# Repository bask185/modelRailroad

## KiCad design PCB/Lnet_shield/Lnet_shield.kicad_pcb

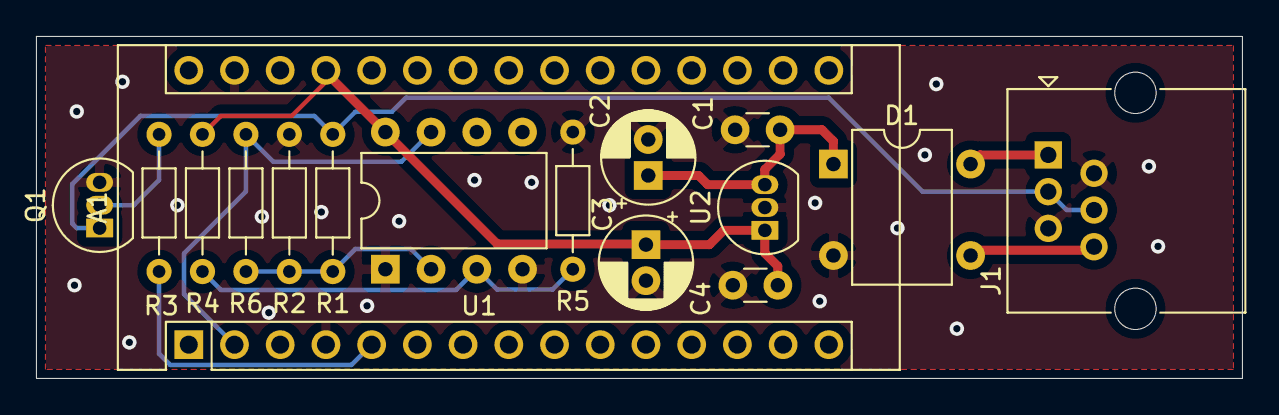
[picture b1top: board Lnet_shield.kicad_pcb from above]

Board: 2 copper layers, 67.0 x 19.0 mm, 16 parts (0 on the bottom side), 11 nets.

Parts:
A1: Arduino_Nano_v2.x; Arduino_Nano
C1, C4: C; C_Disc_D3.0mm_W1.6mm_P2.50mm
C2, C3: CP; CP_Radial_D5.0mm_P2.00mm
D1: D_Bridge_+-AA; Diode_Bridge_DIP-4_W7.62mm_P5.08mm
J1: RJ12; RJ25_Wayconn_MJEA-660X1_Horizontal
Q1: BC547; TO-92_Inline
R1: 47k; R_Axial_DIN0204_L3.6mm_D1.6mm_P7.62mm_Horizontal
R2: 150k; R_Axial_DIN0204_L3.6mm_D1.6mm_P7.62mm_Horizontal
R3: 4k7; R_Axial_DIN0204_L3.6mm_D1.6mm_P7.62mm_Horizontal
R4: 10k; R_Axial_DIN0204_L3.6mm_D1.6mm_P7.62mm_Horizontal
R5: 22k; R_Axial_DIN0204_L3.6mm_D1.6mm_P7.62mm_Horizontal
R6: 220k; R_Axial_DIN0204_L3.6mm_D1.6mm_P7.62mm_Horizontal
U1: LM311; DIP-8_W7.62mm
U2: L78L05_TO92; TO-92_Inline

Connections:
+5V: A1.27, C3.1, C4.1, R4.2, U1.8, U2.1
+12V: C1.1, C2.1, D1.1, U2.3
/Lnet: J1.3, J1.4, Q1.1, R1.2
/Rx: A1.2, R6.1, U1.7
/Tx: A1.5, R3.1
GND: A1.4, A1.29, C1.2, C2.2, C3.2, C4.2, D1.2, J1.2, J1.5, Q1.3, R2.1, R5.1, U1.1, U1.4, U2.2
unnamed: D1.3, J1.6
unnamed: D1.4, J1.1
unnamed: Q1.2, R3.2
unnamed: R1.1, R2.2, R6.2, U1.2
unnamed: R4.1, R5.2, U1.3

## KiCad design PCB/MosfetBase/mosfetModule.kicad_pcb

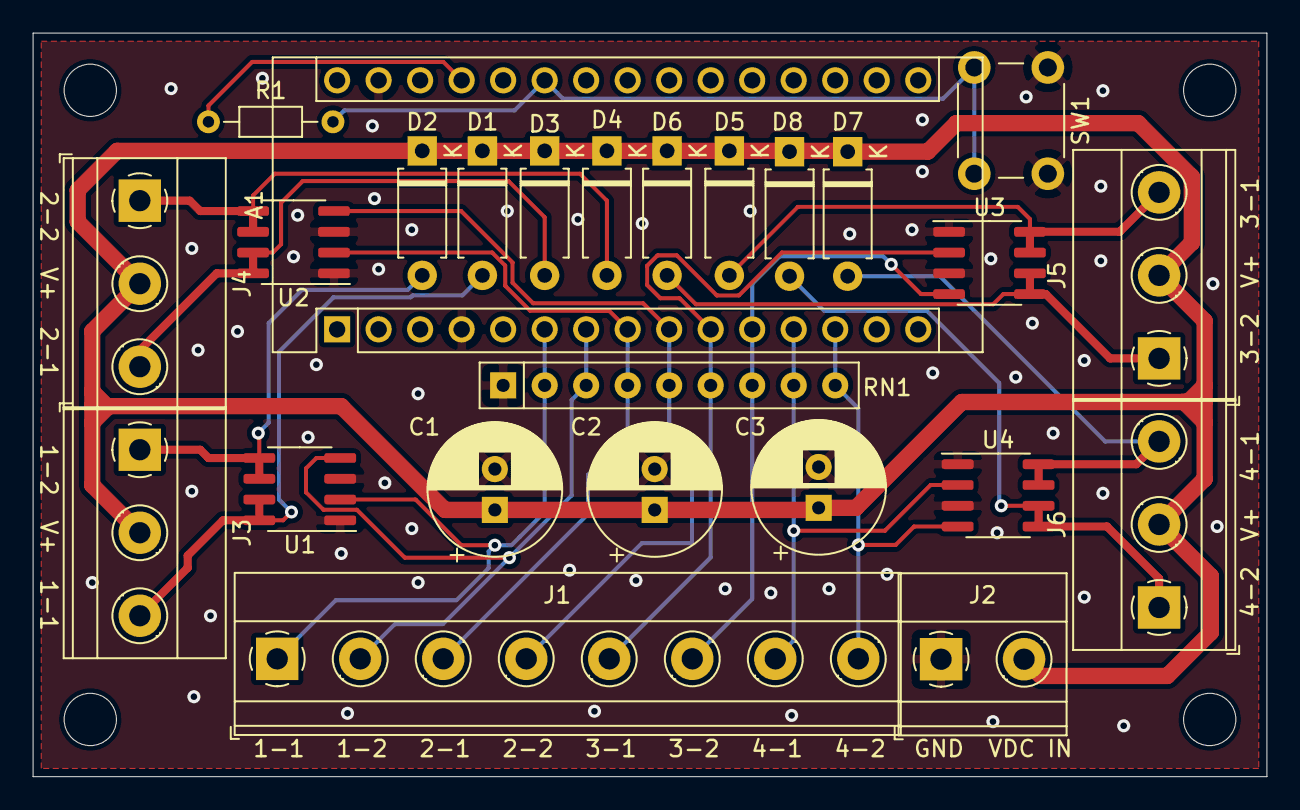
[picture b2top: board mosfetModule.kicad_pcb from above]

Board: 2 copper layers, 75.5 x 45.5 mm, 25 parts (0 on the bottom side), 20 nets.

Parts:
A1: Arduino_Nano_v3.x; Arduino_Nano
C1, C2, C3: CP; CP_Radial_D8.0mm_P2.50mm
D1, D2, D3, D4, D5, D6, D7, D8: D; D_A-405_P7.62mm_Horizontal
J1: toDCCnext; TerminalBlock_Phoenix_MKDS-1,5-8-5.08_1x08_P5.08mm_Horizont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
J2: power; TerminalBlock_Phoenix_MKDS-1,5-2-5.08_1x02_P5.08mm_Horizont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
J3, J4, J5, J6: point; TerminalBlock_Phoenix_MKDS-1,5-3-5.08_1x03_P5.08mm_Horizont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
R1: R; R_Axial_DIN0204_L3.6mm_D1.6mm_P7.62mm_Horizontal
RN1: R; R_Array_SIP9
SW1: SW_SPST; SW_PUSH_6mm_H4.3mm
U1, U2, U3, U4: IRF71xx; SOIC-8_3.9x4.9mm_P1.27mm

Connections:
+5V: A1.27, R1.1
/coil1-1: D1.2, J3.3, U1.7, U1.8
/coil1-2: D2.2, J3.1, U1.5, U1.6
/coil2-1: D3.2, J4.3, U2.7, U2.8
/coil2-2: D4.2, J4.1, U2.5, U2.6
/coil3-1: D5.2, J5.3, U3.7, U3.8
/coil3-2: D6.2, J5.1, U3.5, U3.6
/coil4-1: D7.2, J6.3, U4.7, U4.8
/coil4-2: D8.2, J6.1, U4.5, U4.6
/in1-1: A1.6, J1.1, RN1.2, U1.2
/in1-2: A1.7, J1.2, RN1.3, U1.4
/in2-1: A1.8, J1.3, RN1.4, U2.2
/in2-2: A1.9, J1.4, RN1.5, U2.4
/in3-1: A1.10, J1.5, RN1.6, U3.2
/in3-2: A1.11, J1.6, RN1.7, U3.4
/in4-1: A1.12, J1.7, RN1.8, U4.2
/in4-2: A1.13, J1.8, RN1.9, U4.4
GND: A1.4, A1.29, C1.2, C2.2, C3.2, J2.1, RN1.1, SW1.1, U1.1, U1.3, U2.1, U2.3, U3.1, U3.3, U4.1, U4.3
unnamed: A1.25, R1.2, SW1.2
VCC: C1.1, C2.1, C3.1, D1.1, D2.1, D3.1, D4.1, D5.1, D6.1, D7.1, D8.1, J2.2, J3.2, J4.2, J5.2, J6.2

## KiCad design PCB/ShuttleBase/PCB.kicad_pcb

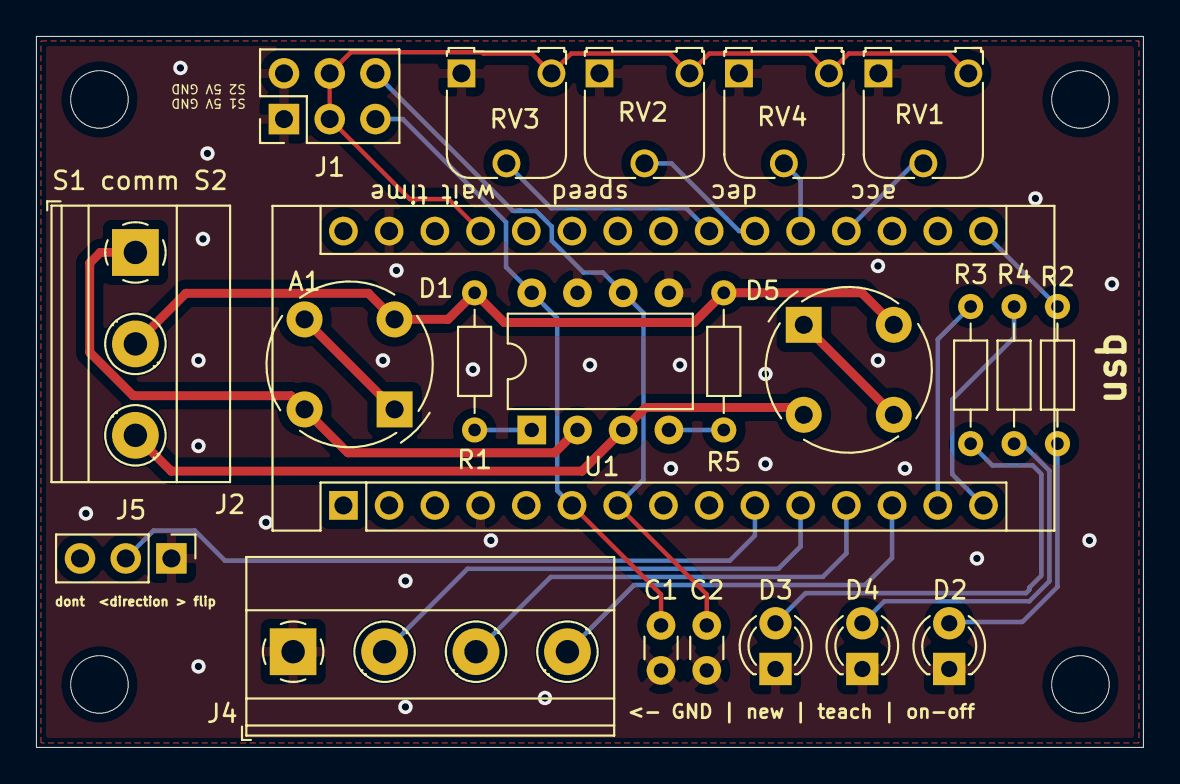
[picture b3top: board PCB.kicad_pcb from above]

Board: 2 copper layers, 61.5 x 39.5 mm, 22 parts (0 on the bottom side), 25 nets.

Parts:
A1: Arduino_Nano_v2.x; Arduino_Nano
C1, C2: C; C_Disc_D3.0mm_W1.6mm_P2.50mm
D1, D5: D; Diode_Bridge_Round_D9.0mm
D2: RED; LED_D3.0mm
D3: GREEN; LED_D3.0mm
D4: YEL; LED_D3.0mm
J1: IR; PinHeader_2x03_P2.54mm_Vertical
J2: detectors; TerminalBlock_Phoenix_MKDS-1,5-3-5.08_1x03_P5.08mm_Horizont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
J4: switches; TerminalBlock_Phoenix_MKDS-1,5-4-5.08_1x04_P5.08mm_Horizont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
J5: directionFlip; PinHeader_1x03_P2.54mm_Vertical
R1, R2, R3, R4, R5: R; R_Axial_DIN0204_L3.6mm_D1.6mm_P7.62mm_Horizontal
RV1, RV2, RV3, RV4: R_POT; Potentiometer_Runtron_RM-065_Vertical
U1: PC827; DIP-8_W7.62mm

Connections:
+5V: A1.27, J1.3, J1.4, RV1.3, RV2.3, RV3.3, RV4.3
/ON_OFF: A1.13, J4.4
/accel: A1.20, RV4.2
/brake: A1.19, RV1.2
/direction: A1.10, J5.2
/greenStatus: A1.14, R3.1
/newTrain: A1.11, J4.2
/redStatus: A1.16, R2.1
/sensor1: A1.6, C1.1, J1.5, U1.8
/sensor2: A1.7, C2.1, J1.6, U1.6
/speed: A1.21, RV2.2
/teach: A1.12, J4.3
/wait: A1.22, RV3.2
/yellowStatus: A1.15, R4.1
GND: A1.4, A1.29, C1.2, C2.2, D2.1, D3.1, D4.1, J1.1, J1.2, J4.1, J5.1, RV1.1, RV2.1, RV3.1, RV4.1, U1.5, U1.7
unnamed: D1.1, D1.3
unnamed: D1.2, D5.4, J2.2, R1.1, R5.2
unnamed: D1.4, J2.1, U1.2
unnamed: D2.2, R2.2
unnamed: D3.2, R3.2
unnamed: D4.2, R4.2
unnamed: D5.1, D5.3
unnamed: D5.2, J2.3, U1.3
unnamed: R1.2, U1.1
unnamed: R5.1, U1.4

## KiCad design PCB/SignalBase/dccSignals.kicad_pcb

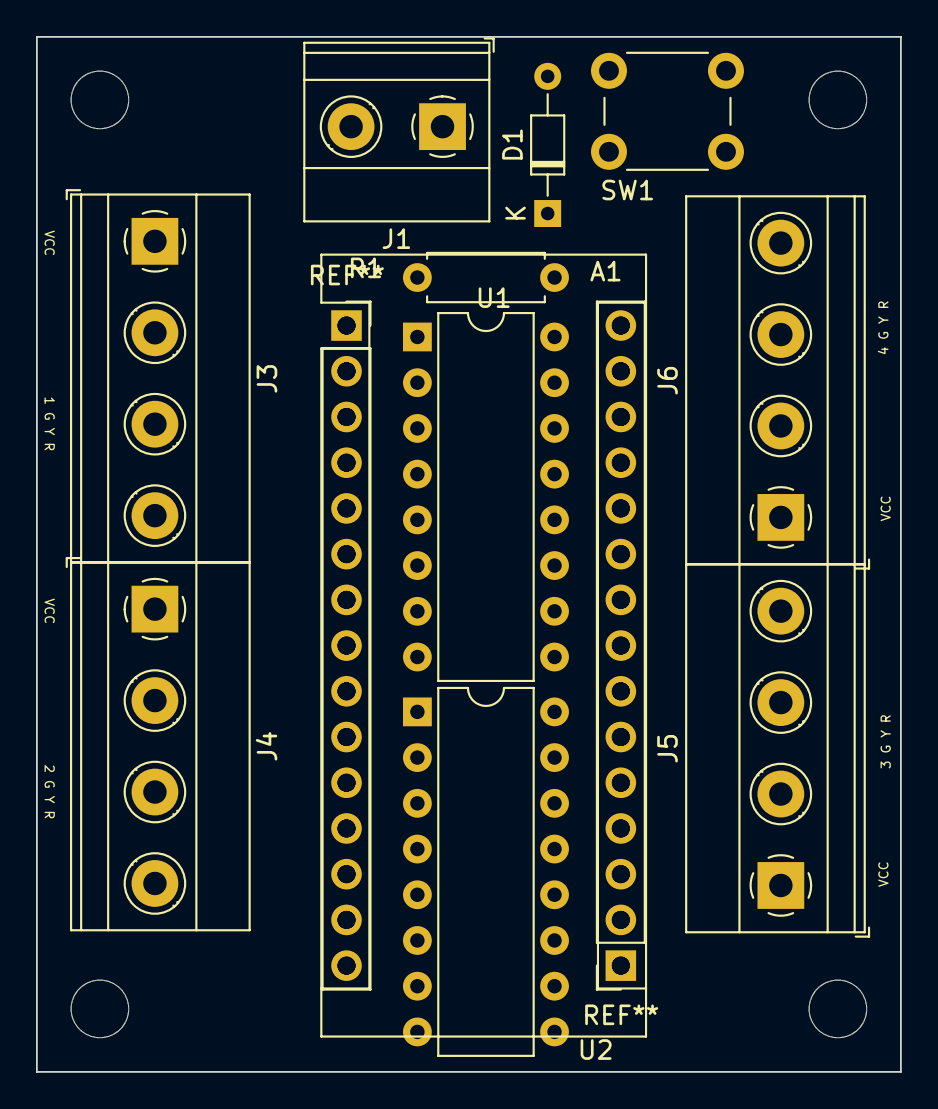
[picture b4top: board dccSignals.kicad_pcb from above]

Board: 2 copper layers, 48.0 x 57.5 mm, 11 parts (0 on the bottom side), 29 nets, no tracks yet.

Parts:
A1: Arduino_Nano_v2.x; Arduino_Nano
D1: D; D_DO-34_SOD68_P7.62mm_Horizontal
J1: Screw_Terminal_01x02; TerminalBlock_Phoenix_MKDS-1,5-2-5.08_1x02_P5.08mm_Horizont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
J3, J4, J5, J6: leds; TerminalBlock_Phoenix_MKDS-1,5-4-5.08_1x04_P5.08mm_Horizont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
R1: R; R_Axial_DIN0207_L6.3mm_D2.5mm_P7.62mm_Horizontal
SW1: SW_SPST; SW_PUSH_6mm_H4.3mm
U1, U2: ULN2003A; DIP-16_W7.62mm

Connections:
+5V: A1.27, R1.1
/S1G: J3.2, U1.16
/S1G_IN: A1.6, U1.1
/S1R: J3.4, U1.14
/S1R_IN: A1.8, U1.3
/S1Y: J3.3, U1.15
/S1Y_IN: A1.7, U1.2
/S2G: J4.2, U1.13
/S2G_IN: A1.9, U1.4
/S2R: J4.4, U1.11
/S2R_IN: A1.11, U1.6
/S2Y: J4.3, U1.12
/S2Y_IN: A1.10, U1.5
/S3G: J5.2, U2.11
/S3G_IN: A1.16, U2.6
/S3R: J5.4, U2.13
/S3R_IN: A1.15, U2.4
/S3Y: J5.3, U2.12
/S3Y_IN: A1.24, U2.5
/S4G: J6.2, U2.14
/S4G_IN: A1.12, U2.1
/S4R: J6.4, U2.16
/S4R_IN: A1.14, U2.3
/S4Y: J6.3, U2.15
/S4Y_IN: A1.13, U2.2
GND: A1.4, A1.29, J1.2, SW1.2, U1.8, U2.8
unnamed: A1.25, R1.2, SW1.1
unnamed: D1.2, J1.1
VCC: D1.1, J3.1, J4.1, J5.1, J6.1, U1.9, U2.9

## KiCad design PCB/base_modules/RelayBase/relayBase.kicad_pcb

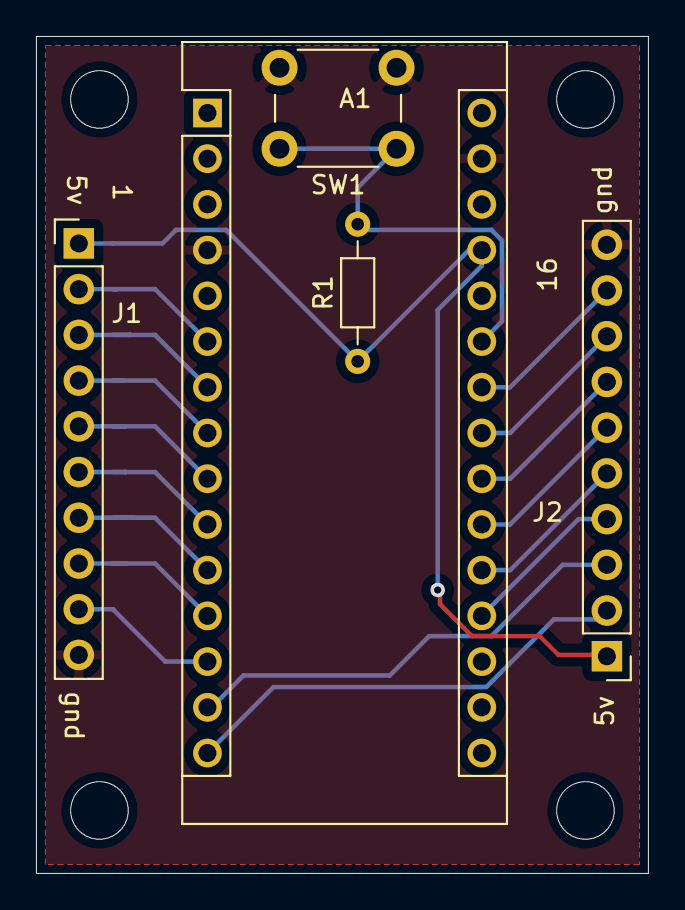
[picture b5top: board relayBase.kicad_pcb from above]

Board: 2 copper layers, 34.0 x 46.5 mm, 5 parts (0 on the bottom side), 19 nets.

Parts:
A1: Arduino_Nano_v3.x; Arduino_Nano
J1, J2: Conn_01x10_Male; PinHeader_1x10_P2.54mm_Vertical
R1: R; R_Axial_DIN0204_L3.6mm_D1.6mm_P7.62mm_Horizontal
SW1: SW_SPST; SW_PUSH_6mm_H4.3mm

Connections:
+5V: A1.27, J1.1, J2.1, R1.1
/in1: A1.13, J1.9
/in2: A1.12, J1.8
/in3: A1.11, J1.7
/in4: A1.10, J1.6
/in5: A1.9, J1.5
/in6: A1.8, J1.4
/in7: A1.7, J1.3
/in8: A1.6, J1.2
/in9: A1.24, J2.9
/in10: A1.23, J2.8
/in11: A1.22, J2.7
/in12: A1.21, J2.6
/in13: A1.20, J2.5
/in14: A1.19, J2.4
/in15: A1.14, J2.3
/in16: A1.15, J2.2
GND: A1.4, A1.29, J1.10, J2.10, SW1.2
unnamed: A1.25, R1.2, SW1.1

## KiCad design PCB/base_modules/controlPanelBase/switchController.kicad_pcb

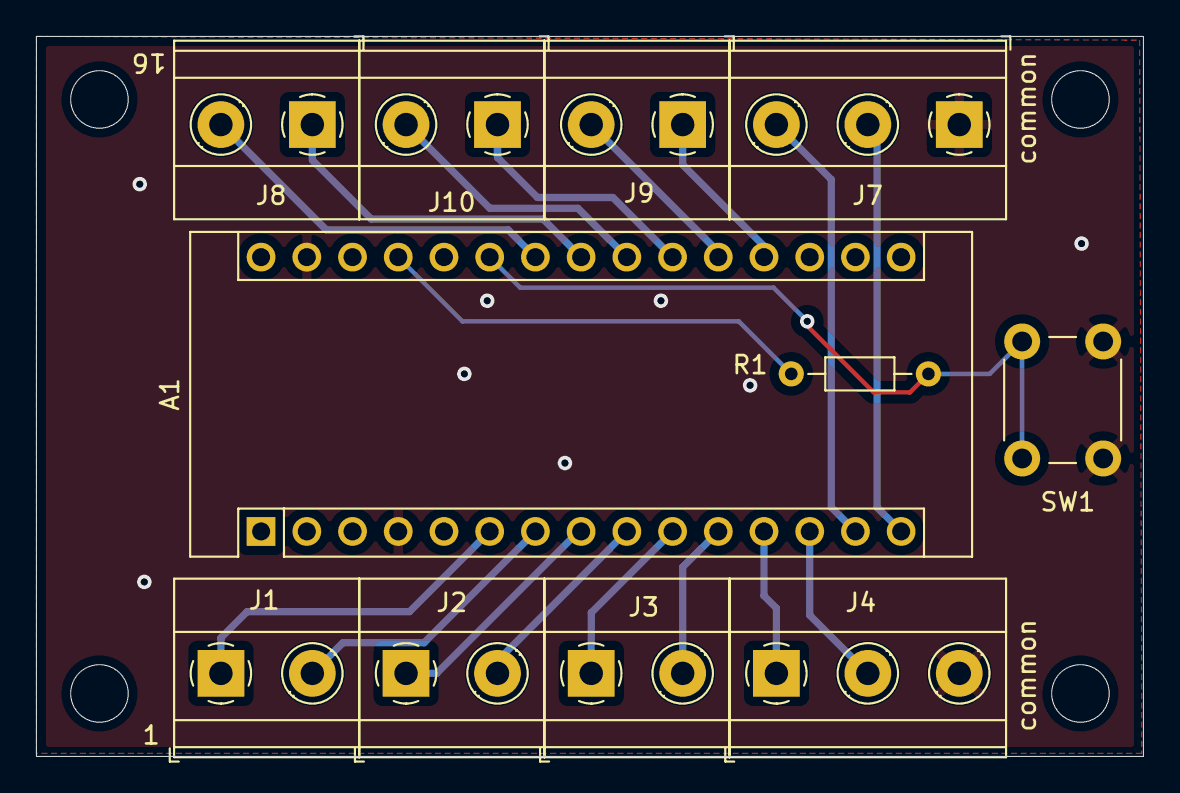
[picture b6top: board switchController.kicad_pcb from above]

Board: 2 copper layers, 61.5 x 40.0 mm, 11 parts (0 on the bottom side), 19 nets.

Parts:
A1: Arduino_Nano_v3.x; Arduino_Nano
J1, J2, J3, J8, J9, J10: i; TerminalBlock_Phoenix_MKDS-1,5-2-5.08_1x02_P5.08mm_Horizont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
J4, J7: i; TerminalBlock_Phoenix_MKDS-1,5-3-5.08_1x03_P5.08mm_Horizont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
R1: R; R_Axial_DIN0204_L3.6mm_D1.6mm_P7.62mm_Horizontal
SW1: SW_SPST; SW_PUSH_6mm_H4.3mm

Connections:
+5V: A1.27, R1.1
GND: A1.4, A1.29, J4.3, J7.1, SW1.1
unnamed: A1.6, J1.1
unnamed: A1.7, J1.2
unnamed: A1.8, J2.1
unnamed: A1.9, J2.2
unnamed: A1.10, J3.1
unnamed: A1.11, J3.2
unnamed: A1.12, J4.1
unnamed: A1.13, J4.2
unnamed: A1.14, J7.3
unnamed: A1.15, J7.2
unnamed: A1.19, J9.1
unnamed: A1.20, J9.2
unnamed: A1.21, J10.1
unnamed: A1.22, J10.2
unnamed: A1.23, J8.1
unnamed: A1.24, J8.2
unnamed: A1.25, R1.2, SW1.2

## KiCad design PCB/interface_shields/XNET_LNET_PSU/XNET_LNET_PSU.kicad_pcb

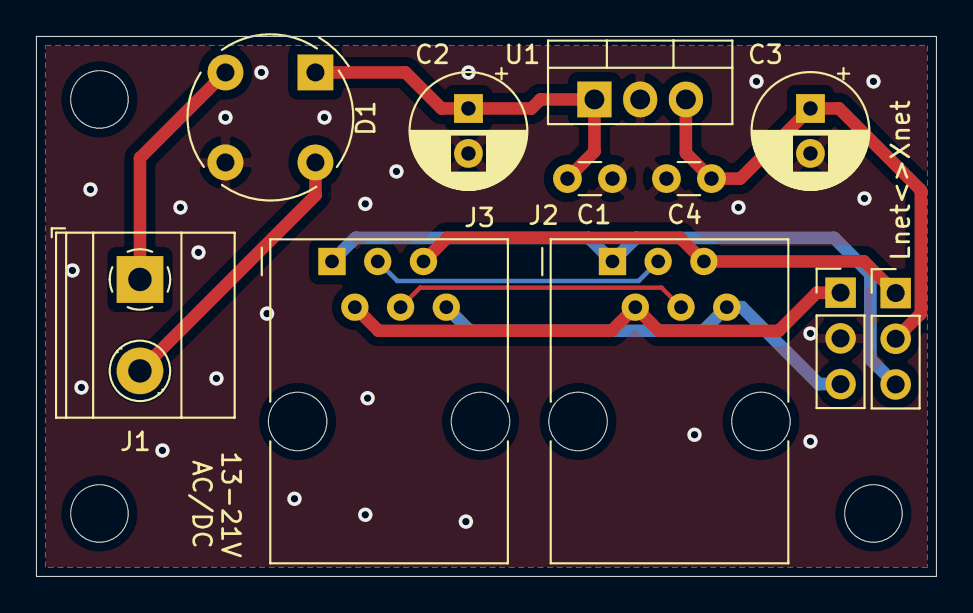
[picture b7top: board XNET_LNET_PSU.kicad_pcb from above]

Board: 2 copper layers, 50.0 x 30.0 mm, 11 parts (0 on the bottom side), 11 nets.

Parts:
C1, C4: C; C_Disc_D3.0mm_W1.6mm_P2.50mm
C2, C3: CP; CP_Radial_D6.3mm_P2.50mm
D1: D_Bridge_+A-A; Diode_Bridge_Round_D9.0mm
J1: power; TerminalBlock_Phoenix_MKDS-1,5-2-5.08_1x02_P5.08mm_Horizont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
J2, J3: RJ12; RJ12_Amphenol_54601
SW1, SW2: SW_SPDT; PinHeader_1x03_P2.54mm_Vertical
U1: LM7812_TO220; TO-220-3_Vertical

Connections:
+12V: C3.1, C4.1, SW2.2, U1.3
GND: C1.2, C2.2, C3.2, C4.2, D1.3, SW1.2, U1.2
unnamed: C1.1, C2.1, D1.1, U1.1
unnamed: D1.2, J1.1
unnamed: D1.4, J1.2
unnamed: J2.1, J3.1, SW2.3
unnamed: J2.2, J3.2, SW1.1
unnamed: J2.3, J3.3
unnamed: J2.4, J3.4
unnamed: J2.5, J3.5, SW2.1
unnamed: J2.6, J3.6, SW1.3

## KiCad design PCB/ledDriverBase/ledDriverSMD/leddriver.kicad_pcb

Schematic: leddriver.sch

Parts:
C1, C2: CP; CP_Elec_4x4.5
C3: C; C_0805_2012Metric
D1: MB6S; TO-269AA
J1: Screw_Terminal_01x04; TerminalBlock_Phoenix_MKDS-1,5-4-5.08_1x04_P5.08mm_Horizont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
J2: switches; TerminalBlock_bornier-6_P5.08mm
J3, J4: Screw_Terminal_01x03; TerminalBlock_Phoenix_MKDS-1,5-6-5.08_1x06_P5.08mm_Horizont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
J5: encoder; PinHeader_1x05_P2.54mm_Vertical
J6: ICSP; PinHeader_2x03_P1.27mm_Vertical
R1, R2, R3, R4, R5, R6: 220R; R_0805_2012Metric
U1: ATmega328PB-MU; QFN-32-1EP_5x5mm_P0.5mm_EP3.1x3.1mm
U2: ULN2003A; SOIC-16_3.9x9.9mm_P1.27mm
U3: L78L05_SO8; SOIC-8_3.9x4.9mm_P1.27mm
Y1: Crystal; Crystal_SMD_3215-2Pin_3.2x1.5mm

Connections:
+5V: C2.1, C3.1, J5.2, J6.5, R1.2, R2.2, R3.2, R4.2, R5.2, R6.2, U1.4 (VCC), U1.18 (AVCC), U3.1 (OUT)
+12V: C1.1, D1.3 (+), J1.2, U2.9 (COM), U3.8 (IN)
/Sw1: J2.1, U1.28 (PC5)
/Sw2: J2.2, U1.27 (PC4)
/Sw3: J2.3, U1.26 (PC3)
/Sw4: J2.4, U1.25 (PC2)
/Sw5: J2.5, U1.24 (PC1)
/Sw6: J2.6, U1.23 (PC0)
/btn: J5.3, U1.32 (PD2)
/clock: J5.5, U1.2 (PD4)
/data: J5.4, U1.11 (PD7)
/miso: J6.6, U1.16 (PB4)
/mosi: J6.3, U1.15 (PB3), U2.5 (I5)
/pwm1: U1.1 (PD3), U2.6 (I6)
/pwm2: U1.9 (PD5), U2.1 (I1)
/pwm3: U1.10 (PD6), U2.2 (I2)
/pwm5: U1.14 (PB2), U2.4 (I4)
/pwm6: U1.13 (PB1), U2.3 (I3)
/reset: J6.2, U1.29 (~RESET~/PC6)
/sck: J6.4, U1.17 (PB5)
GND: C1.2, C2.2, C3.2, D1.4 (-), J1.1, J5.1, J6.1, U1.5 (GND), U1.21 (GND), U1.33 (GND), U2.8 (GND), U3.2 (GND), U3.3 (GND), U3.6 (GND), U3.7 (GND)
unnamed: D1.1 (~~), J1.4
unnamed: D1.2 (~~), J1.3
unnamed: J3.1, U2.13 (O4)
unnamed: J3.2, R3.1
unnamed: J3.3, U2.12 (O5)
unnamed: J3.4, R2.1
unnamed: J3.5, U2.11 (O6)
unnamed: J3.6, R1.1
unnamed: J4.1, U2.16 (O1)
unnamed: J4.2, R6.1
unnamed: J4.3, U2.15 (O2)
unnamed: J4.4, R5.1
unnamed: J4.5, U2.14 (O3)
unnamed: J4.6, R4.1
unnamed: U1.7 (XTAL1/PB6), Y1.1
unnamed: U1.8 (XTAL2/PB7), Y1.2

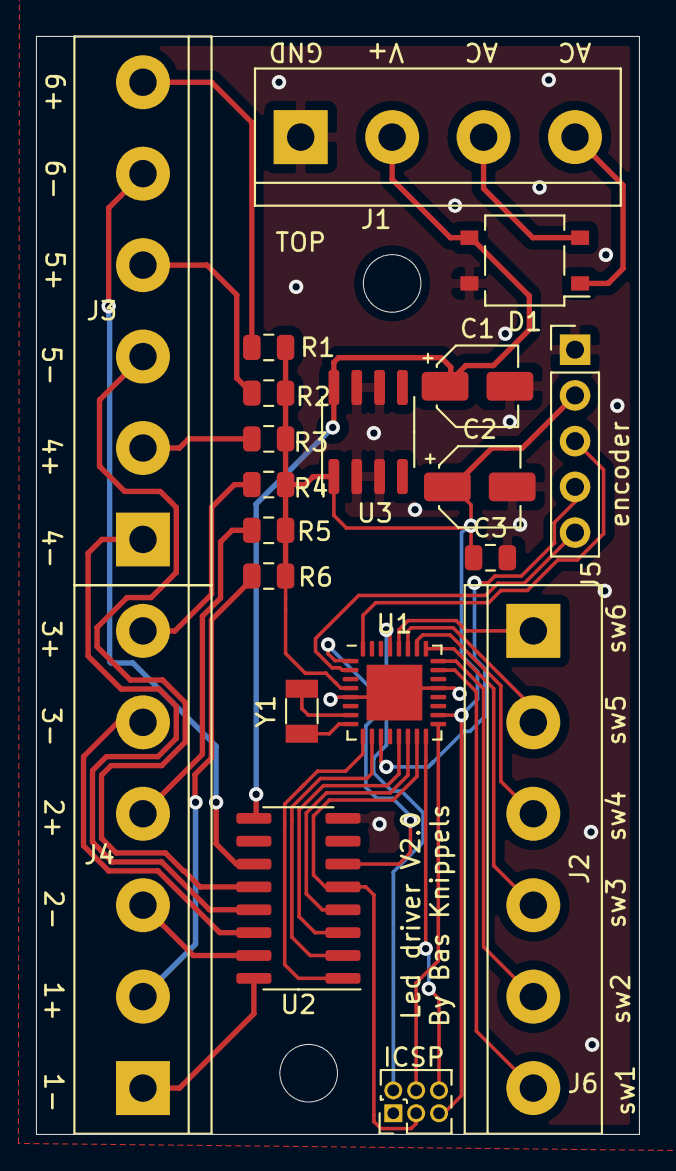
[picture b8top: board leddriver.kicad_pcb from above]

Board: 2 copper layers, 33.5 x 61.0 mm, 20 parts (0 on the bottom side), 37 nets.
